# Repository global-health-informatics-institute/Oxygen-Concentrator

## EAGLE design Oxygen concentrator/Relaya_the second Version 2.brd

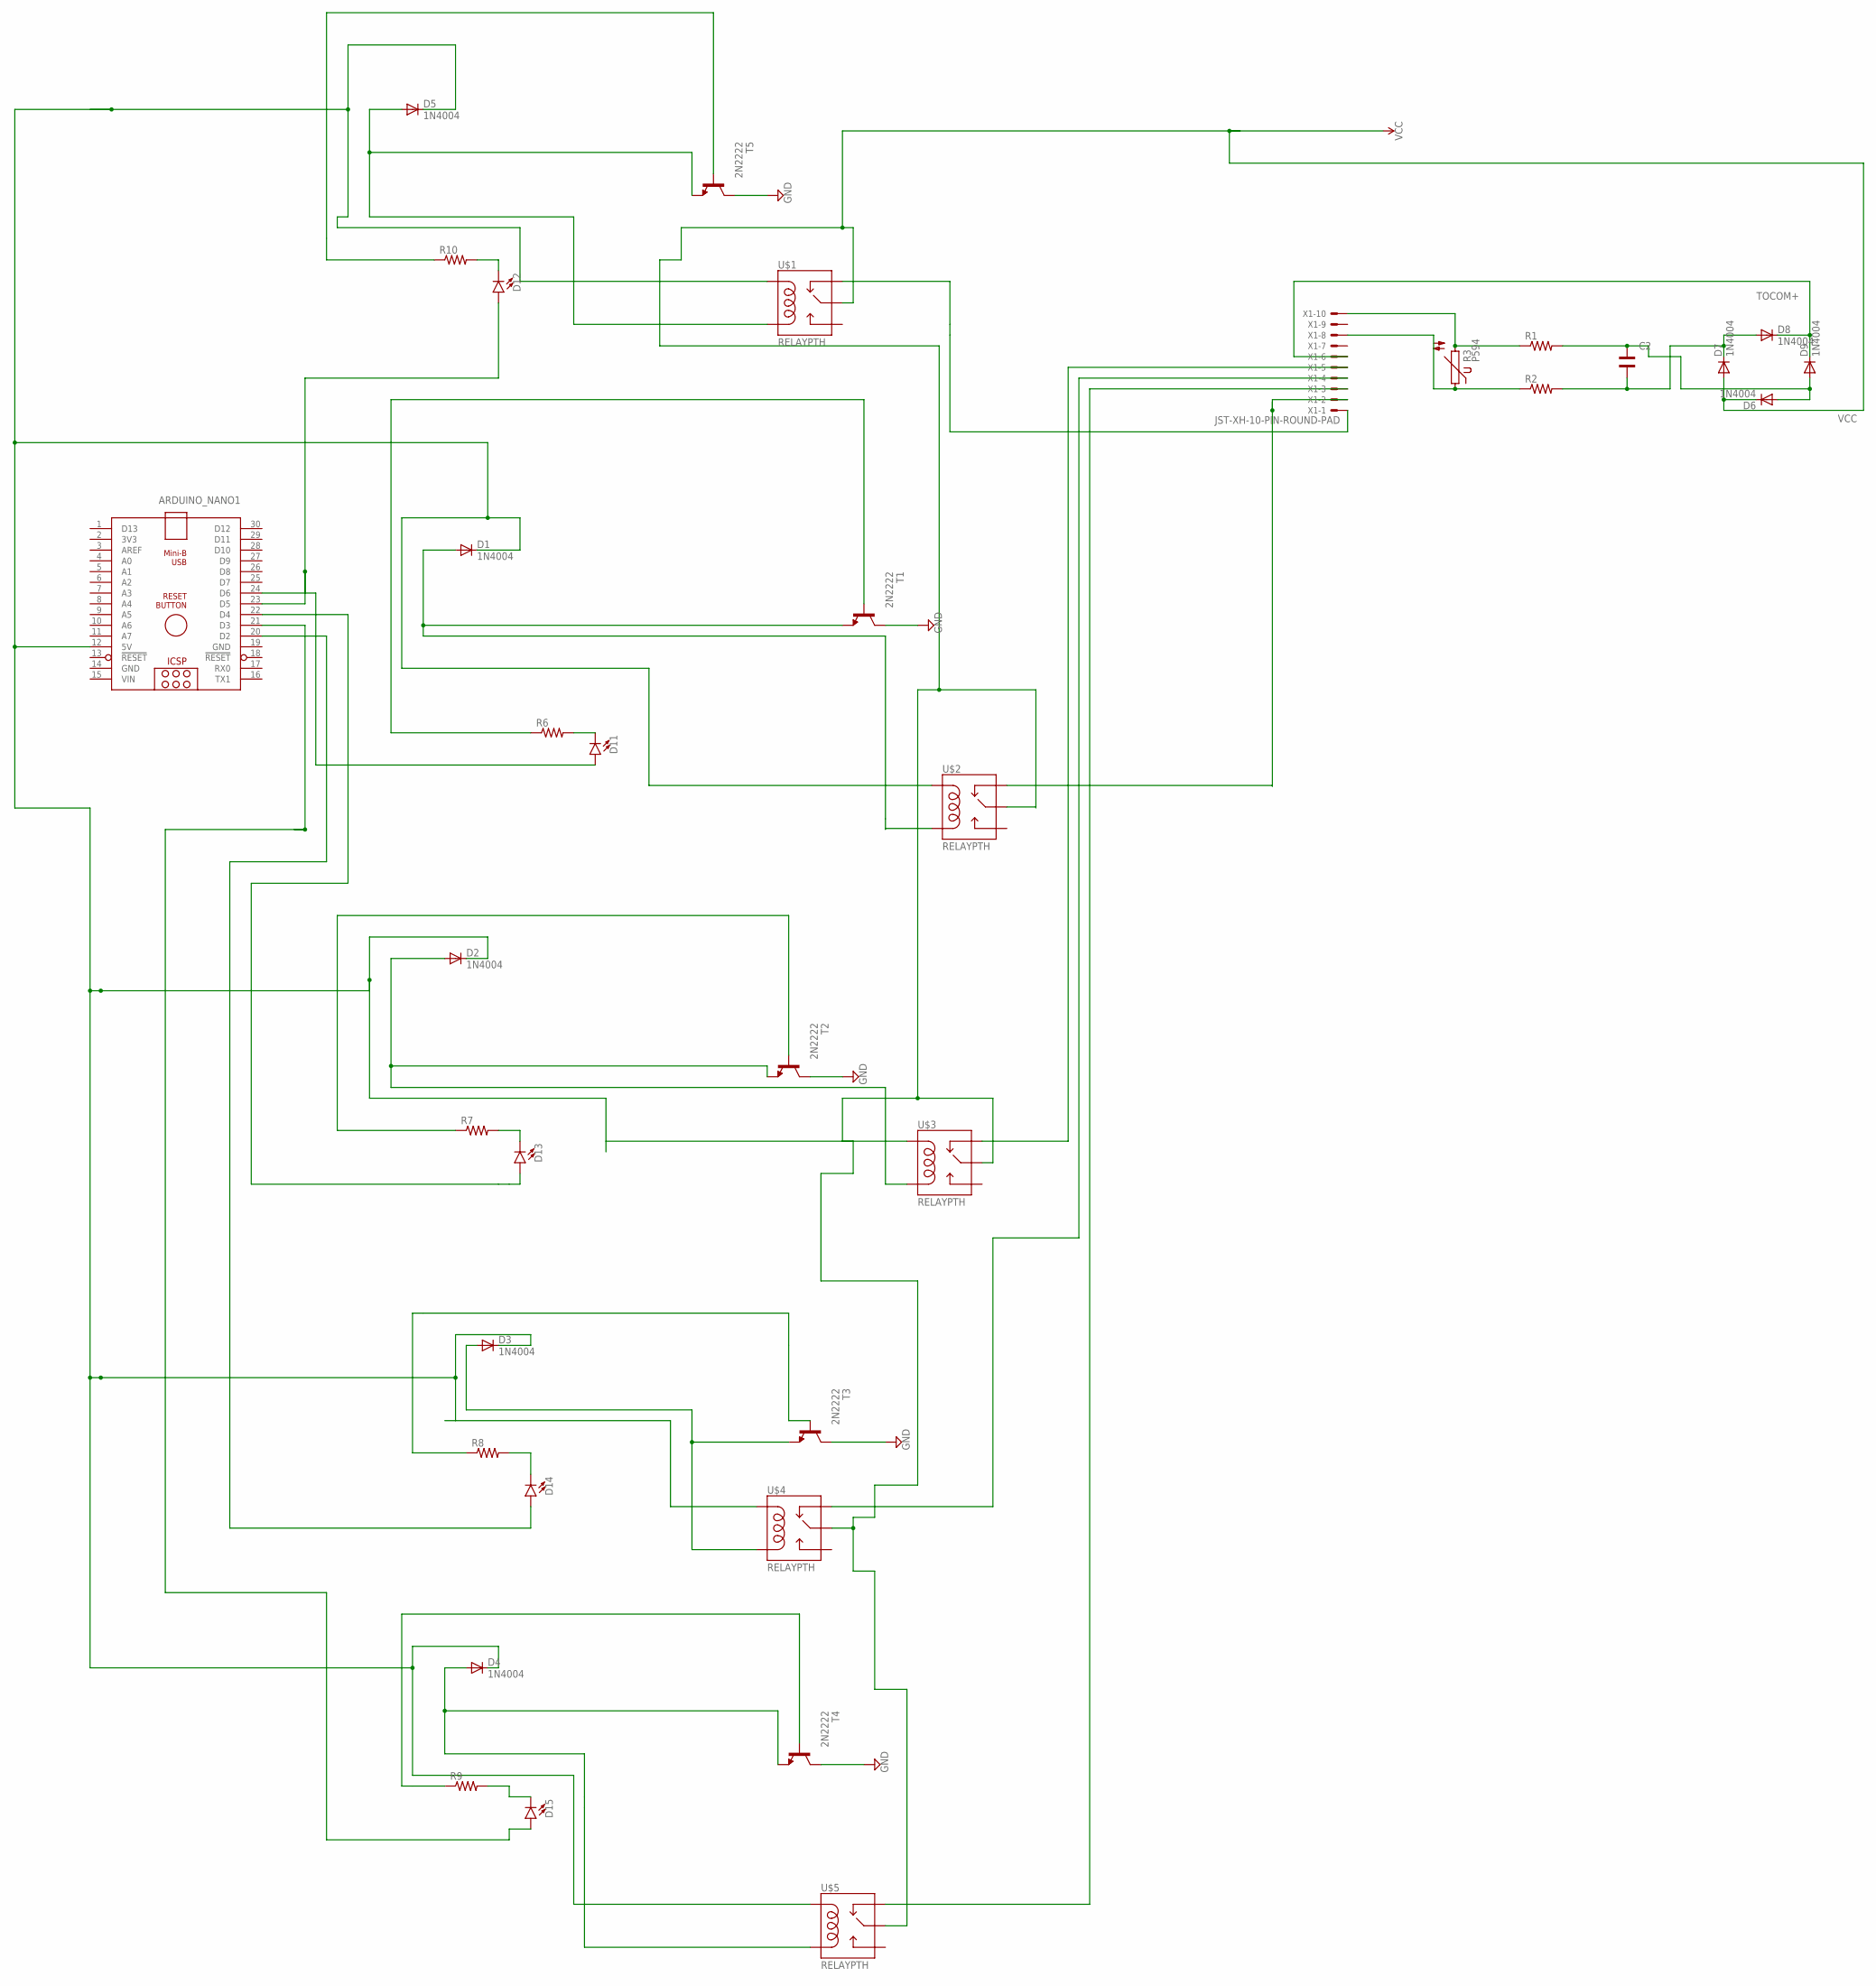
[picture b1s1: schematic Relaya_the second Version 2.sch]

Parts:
ARDUINO_NANO1: ARDUINO_NANO
C2: WCAP-FTBP_890283323005CS; WCAP-FTBX,10X13X5.5X4
D1, D2, D3, D4, D5, D6, D7, D8, D9: 1N4004; DO41-10
D11, D12, D13, D14, D15: LED5MM; LED_5MM
R1, R2: R-US_0414/15; 0414/15
R3: P594
R6, R7, R8, R9, R10: R-US_0207/10; 0207/10
T1, T2, T3, T4, T5: 2N2222; TO92-EBC-OVAL
U$1, U$2, U$3, U$4, U$5: RELAYPTH; SRD-05VDC-SL-C
X1: JST-XH-10-PIN-ROUND-PAD; JST-XH-10-PACKAGE-ROUND-PAD

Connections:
5V: ARDUINO_NANO1.12 (5V), D1.C, D2.C, D3.C, D4.C, D5.C, U$1.COIL1, U$2.COIL1, U$3.COIL1, U$4.COIL1, U$5.COIL1
GND: ARDUINO_NANO1.14 (GND), ARDUINO_NANO1.19 (GND), T1.C, T2.C, T3.C, T4.C, T5.C
unnamed: U$1.SWCLOSED (SWCLOSE), X1.1
unnamed: ARDUINO_NANO1.23 (D5), D12.A
unnamed: R6.1, T1.B
unnamed: U$2.SWCLOSED (SWCLOSE), X1.2
unnamed: D1.A, T1.E, U$2.COIL0
unnamed: ARDUINO_NANO1.24 (D6), D11.A
unnamed: D2.A, T2.E, U$3.COIL0
unnamed: R7.1, T2.B
unnamed: ARDUINO_NANO1.22 (D4), D13.A
unnamed: U$3.SWCLOSED (SWCLOSE), X1.5
unnamed: D3.A, T3.E, U$4.COIL0
unnamed: R8.1, T3.B
unnamed: U$4.SWCLOSED (SWCLOSE), X1.4
unnamed: R10.1, T5.B
unnamed: R1.1, R3.2, X1.10
unnamed: D5.A, T5.E, U$1.COIL0
unnamed: R9.1, T4.B
unnamed: ARDUINO_NANO1.20 (D2), D14.A
unnamed: D4.A, T4.E, U$5.COIL0
unnamed: U$5.SWCLOSED (SWCLOSE), X1.3
unnamed: R2.1, R3.1, X1.8
unnamed: ARDUINO_NANO1.21 (D3), D15.A
unnamed: D12.K (C), R10.2
unnamed: D11.K (C), R6.2
unnamed: D14.K (C), R8.2
unnamed: D13.K (C), R7.2
unnamed: D15.K (C), R9.2
unnamed: C2.1, D7.C, D8.A, R2.2
unnamed: C2.2, D6.A, D9.A, R1.2
TOCOM+: D8.C, D9.C, X1.6
VCC: D6.C, D7.A, U$1.SWCOMMON, U$2.SWCOMMON, U$3.SWCOMMON, U$4.SWCOMMON, U$5.SWCOMMON
VIN: ARDUINO_NANO1.15 (VIN)

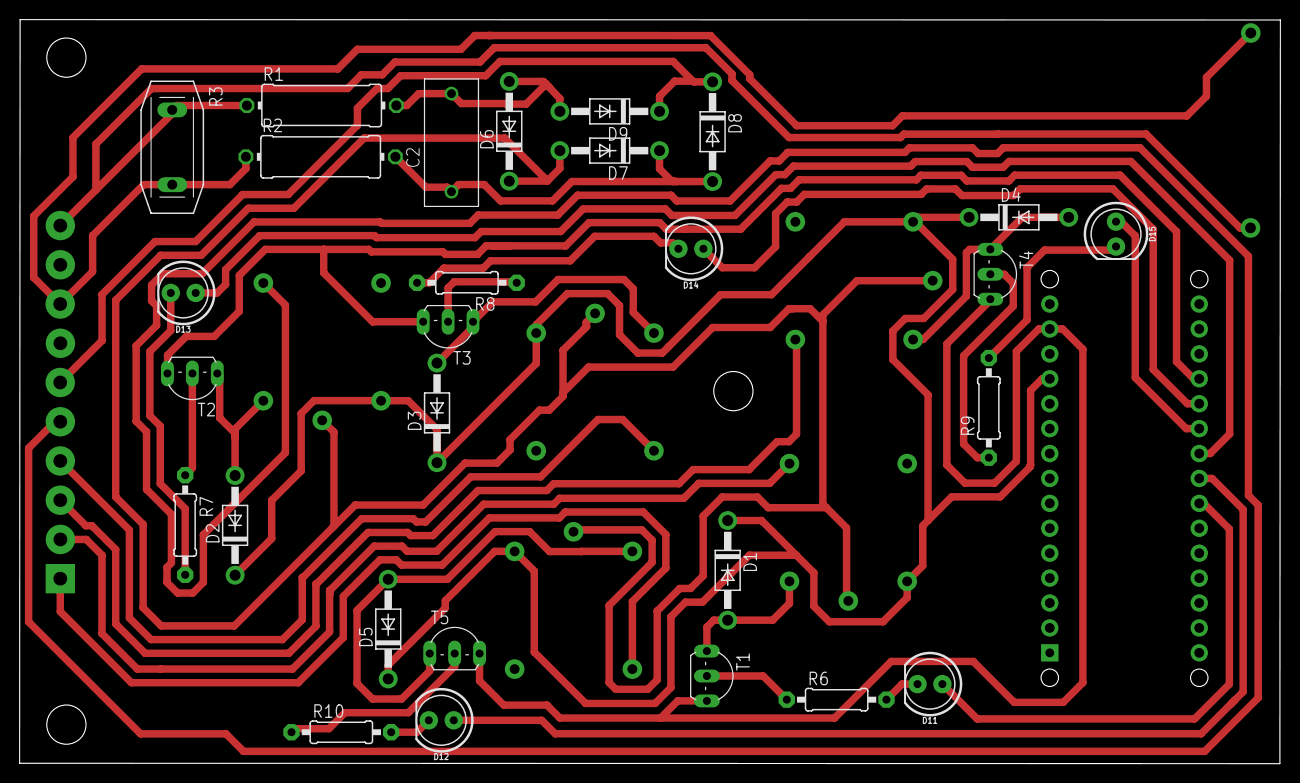
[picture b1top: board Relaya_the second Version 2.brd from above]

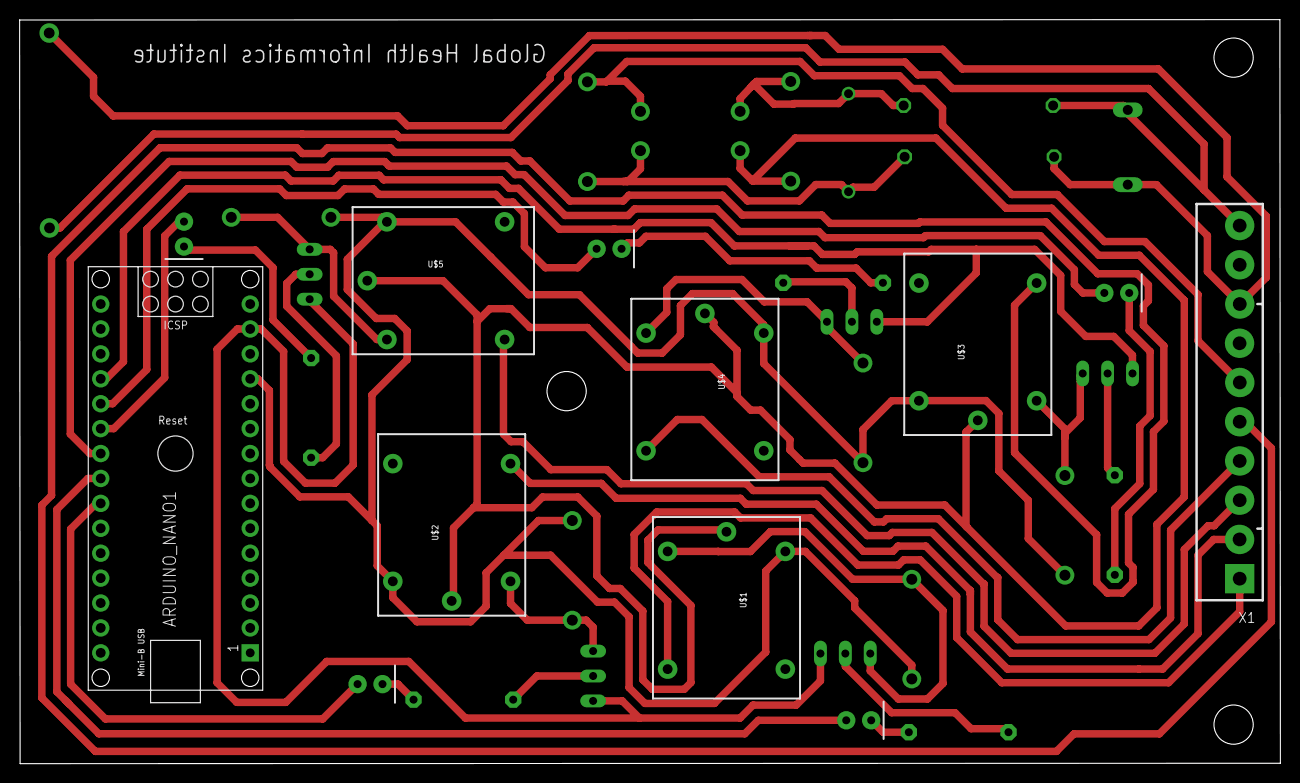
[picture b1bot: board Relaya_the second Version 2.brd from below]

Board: 2 copper layers, 128.5 x 75.9 mm, 35 parts (7 on the bottom side), 33 nets.

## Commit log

2019-07-13 V2 Oxygen concentrator
2020-10-26 Code Measures Oxygen Concentration
2020-11-03 Original code is missing, this is one of the early versions of the code before we got the sequencing right. Needs work on the sequence
2020-11-16 The working version of the code recreated from the sequence provided in the airsep manual
2021-02-21 Oxygen sensor and OLED for Handheld Analyzer
2021-07-19 Valve control for single bed testing
2021-07-19 Oxygen sensor code for single bed testing
2021-07-22 5 way valve control for Airsep

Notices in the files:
parts and their libraries:
SparkFun-LED: Licensing: Creative Commons ShareAlike 4.0 International - https://creativecommons.org/licenses/by-sa/4.0
Wurth_Elektronik_Passive_Capacitors_rev1: Copyright: Würth Elektronik
